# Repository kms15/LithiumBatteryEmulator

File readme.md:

# LithiumBatteryEmulator

This is a PCB that emulates a ~4.2 volt lithium battery cell using power from
a USB connector.  It was designed to replace the battery cell in a Vocera badge
with a wall supplied power supply, but may be useful for other project too.

The board is designed to meet the Seeed studios fusion PCB assembly
requirements, including using the Seeed studio Open Part Library for
KiCad.

## License
Copyright Kendrick Shaw 2020
Licensed under the [CERN OHL v.1.2 license](http://ohwr.org/cernohl).

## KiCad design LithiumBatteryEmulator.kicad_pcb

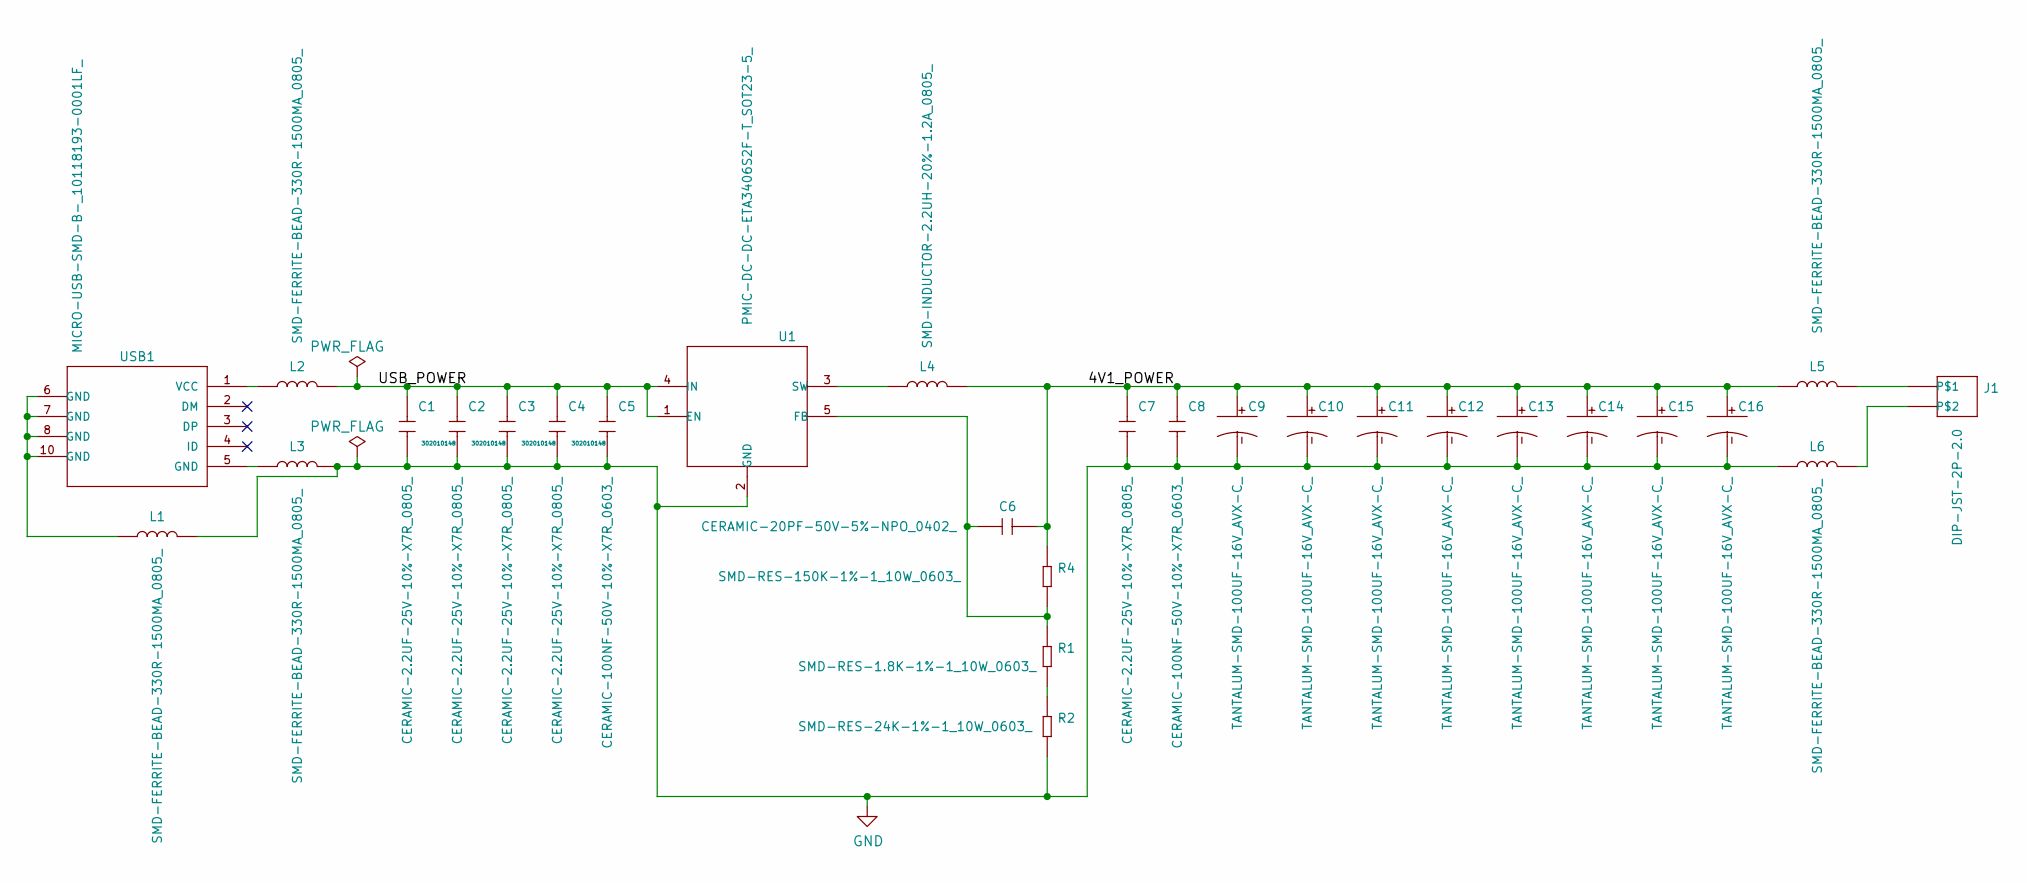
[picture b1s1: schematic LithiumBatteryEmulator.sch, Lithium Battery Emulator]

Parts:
C1, C2, C3, C4, C7: CERAMIC-2.2UF-25V-10%-X7R_0805_; C0805; MPN CC0805KKX7R8BB225
C5, C8: CERAMIC-100NF-50V-10%-X7R_0603_; C0603; MPN CC0603KRX7R9BB104
C6: CERAMIC-20PF-50V-5%-NPO_0402_; C0402; MPN CC0402JRNPO9BN200
C9, C10, C11, C12, C13, C14, C15, C16: TANTALUM-SMD-100UF-16V_AVX-C_; AVX-C(2312); MPN TAJC107K016RNJ
J1: DIP-JST-2P-2.0; H2-2.0-6X4.5MM
L1, L2, L3, L5, L6: SMD-FERRITE-BEAD-330R-1500MA_0805_; L0805; MPN BLM21PG331SN1D
L4: SMD-INDUCTOR-2.2UH-20%-1.2A_0805_; L0805; MPN LQM2MPN2R2MG0
R1: SMD-RES-1.8K-1%-1_10W_0603_; R0603; MPN RC0603FR-071K8L
R2: SMD-RES-24K-1%-1_10W_0603_; R0603; MPN RC0603FR-0724KL
R4: SMD-RES-150K-1%-1_10W_0603_; R0603; MPN RC0603FR-07150KL
U1: PMIC-DC-DC-ETA3406S2F-T_SOT23-5_; SOT-23-5; MPN ETA3406S2F-T
USB1: MICRO-USB-SMD-B-_10118193-0001LF_; MICRO-USB5+6P-SMD-0.65-B; MPN 10118193-0001LF

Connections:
/4V1_POWER: C6.2, C7.1, C8.1, C9.+, C10.+, C11.+, C12.+, C13.+, C14.+, C15.+, C16.+, L4.2, L5.1, R4.1
/USB_POWER: C1.1, C2.1, C3.1, C4.1, C5.1, L2.2, U1.1 (EN), U1.4 (IN)
GND: C1.2, C2.2, C3.2, C4.2, C5.2, C7.2, C8.2, C9.-, C10.-, C11.-, C12.-, C13.-, C14.-, C15.-, C16.-, L1.2, L3.2, L6.1, R2.2, U1.2 (GND)
unnamed: C6.1, R1.1, R4.2, U1.5 (FB)
unnamed: J1.1, L5.2
unnamed: J1.2, L6.2
unnamed: L1.1, USB1.6 (GND), USB1.7 (GND), USB1.8 (GND), USB1.9 (GND), USB1.10 (GND), USB1.11 (GND)
unnamed: L2.1, USB1.1 (VCC)
unnamed: L3.1, USB1.5 (GND)
unnamed: L4.1, U1.3 (SW)
unnamed: R1.2, R2.1

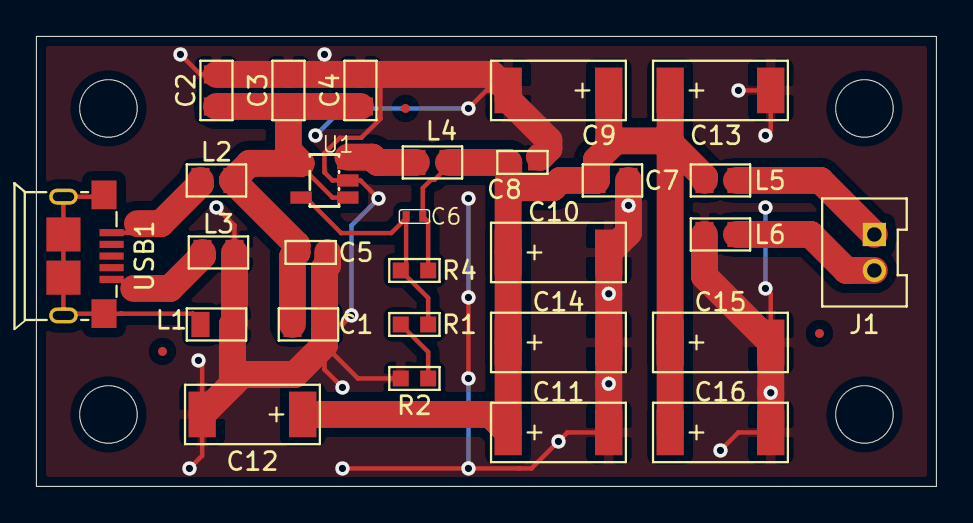
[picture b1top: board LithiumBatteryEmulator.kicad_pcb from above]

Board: 2 copper layers, 50.0 x 25.0 mm, 28 parts (0 on the bottom side), 11 nets.

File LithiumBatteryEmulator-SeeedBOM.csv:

Designator,Manufacturer Part Number or Seeed SKU,Qty,Link
"C10,C11,C12,C13,C14,C15,C16,C9 ",TAJC107K016RNJ,8,https://statics3.seeedstudio.com
"C2,C1,C4,C3,C7 ",CC0805KKX7R8BB225,5,https://statics3.seeedstudio.com
"C5,C8 ",CC0603KRX7R9BB104,2,https://statics3.seeedstudio.com
C6 ,CC0402JRNPO9BN220,1,https://statics3.seeedstudio.com
J1 ,ZB2001-02,1,https://statics3.seeedstudio.com
"L2,L3,L1,L5,L6 ",BLM21PG331SN1D,5,https://statics3.seeedstudio.com
L4 ,LQM2MPN2R2MG0,1,https://statics3.seeedstudio.com
R1 ,RC0603FR-071K8L,1,https://statics3.seeedstudio.com
R2 ,RC0603FR-0724KL,1,https://statics3.seeedstudio.com
R4 ,RC0603FR-07150KL,1,https://statics3.seeedstudio.com
U1 ,ETA3406S2F-T,1,https://statics3.seeedstudio.com
USB1 ,10118193-0001LF,1,https://statics3.seeedstudio.com

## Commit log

2020-01-06 add sheet titles

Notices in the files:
LithiumBatteryEmulator.kicad_pcb:
Licensed under the CERN OHL version 1.2
Licensed under CERN OHL v.1.2
LithiumBatteryEmulator.sch:
Licenced under the CERN OHL version 1.2
